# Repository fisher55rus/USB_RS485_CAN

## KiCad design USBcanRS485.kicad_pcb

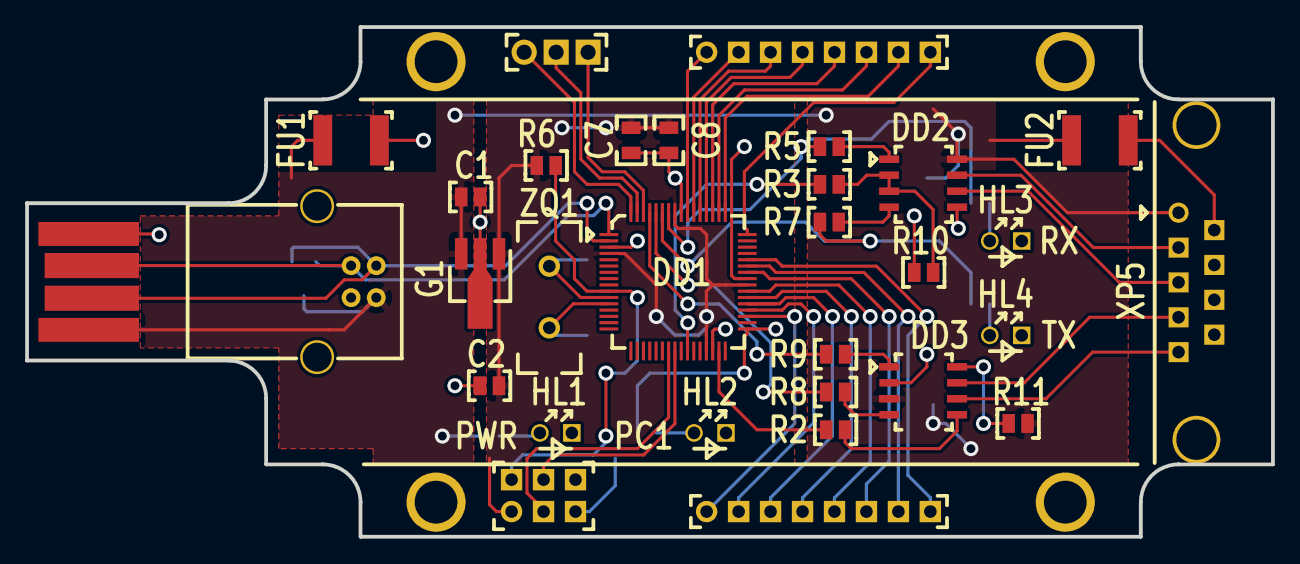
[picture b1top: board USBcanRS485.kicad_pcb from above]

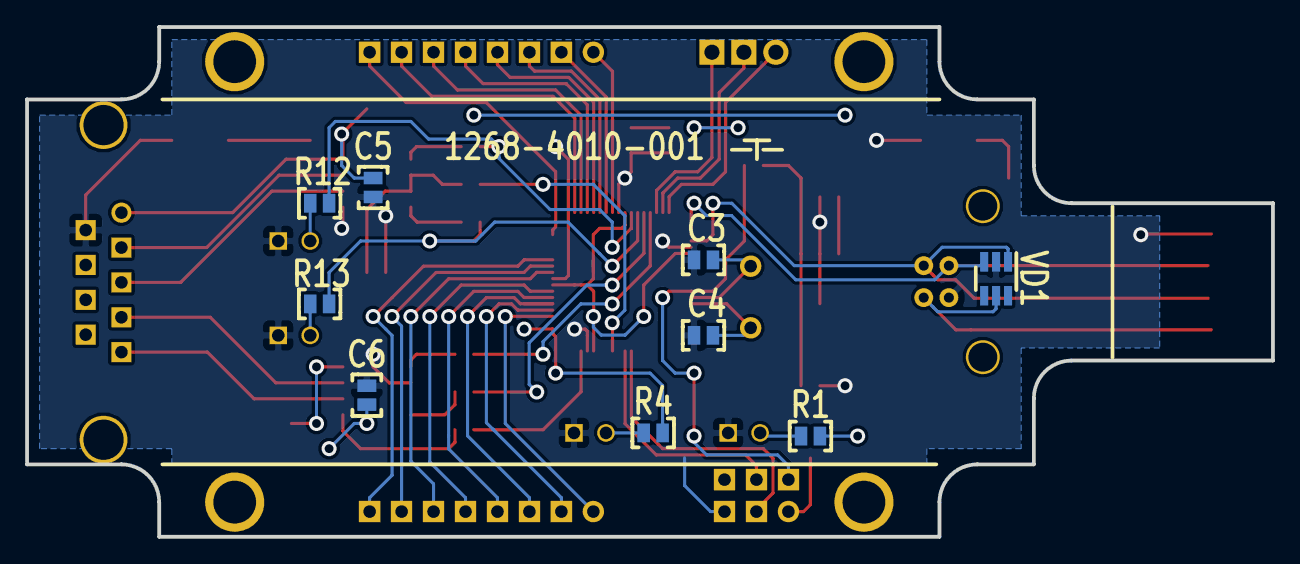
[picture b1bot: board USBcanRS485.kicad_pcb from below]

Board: 2 copper layers, 99.0 x 40.5 mm, 41 parts (10 on the bottom side), 51 nets.

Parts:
C1: 25В-0,33мкФ; Конденсатор_SMD_0603
C2: 25В-0,1мкФ; Конденсатор_SMD_0603
C3, C4: 12пФ; Конденсатор_SMD_0603
C5, C6: 25В-1,5мкФ; Конденсатор_SMD_0603
C7, C8: 16В-10мкФ; Конденсатор_SMD_0805
DD1: 1986ВЕ92; Микросхема_1986ВЕ92QL
DD2: 5559ИН10; SO-8_RS485_CAN_Milandr_OTK
DD3: 5559ИН14; SO-8_RS485_CAN_Milandr_OTK
FU1, FU2: Предохранитель; Fuse_1812
G1: L78L00 SOT-89; SOT-89-3_Handsoldering
HL1, HL2, HL3, HL4: Светодиод; LED_D3.0mm
R1: 100 Ом; Конденсатор_SMD_0603
R2, R3, R5, R7, R8, R9: 240 Ом; Конденсатор_SMD_0603
R4, R12, R13: 15 Ом; Конденсатор_SMD_0603
R6, R10: 20 кОм; Конденсатор_SMD_0603
R11: 24 Ом; Конденсатор_SMD_0603
Ref**: icon_motor_micro; Знак_МОТОР_micro
VD1: ОТК_SP0504S; SOT-23-6_Handsoldering
XP1: Вилка_СНП346-4ВП21-1-В; USB_PLUG
XP2: Вилка_СНП346-6ВП21-1-В; Вилка_PLD6_вертикальная
XP3, XP4: Вилка_СНП346-8ВП21-1-В; Вилка_PLS8_вертикальная
XP5: Вилка_СНП346-6ВП21-1-В; DSUB-9_Female
XP6: Вилка_СНП346-4ВП21-1-В; USB_B
XP7: Вилка_СНП346-3ВП21-1-В
ZQ1: РК456МДУ; Резонатор_РК456МДУ(DIP)

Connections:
3B: C2.1, C7.1, C8.1, DD1.4, DD1.29, DD1.40, DD1.57, G1.1, R6.2, XP2.1
5В: C1.1, C5.1, C6.1, DD2.8, DD3.3, FU1.1, FU2.1, G1.3, R1.2, R11.2, VD1.5, XP1.1, XP5.1, XP6.1
/Osc+: C3.2, DD1.11, ZQ1.1
/Osc-: C4.2, DD1.12, ZQ1.2
A: DD2.6, XP5.3
B: DD2.7, XP5.2
C2RX: DD3.4, R8.2
C2TX: DD3.1, R9.2
D+: DD1.1, VD1.3, XP1.3, XP6.3
D-: DD1.2, VD1.1, XP1.2, XP6.2
GND: C1.2, C2.2, C3.1, C4.1, C5.2, C6.2, C7.2, C8.2, DD1.3, DD1.30, DD1.41, DD1.56, DD2.5, DD3.2, FU1.2, FU2.2, G1.2, HL1.2, HL2.2, HL3.2, HL4.2, R10.2, VD1.2, XP1.4, XP2.5, XP5.6, XP6.4
H: DD3.7, XP5.4
L: DD3.6, XP5.5
unnamed: DD1.26, R3.2
unnamed: DD1.31, R2.2
unnamed: DD1.33, R4.2
unnamed: DD1.58, R5.1, R12.1
unnamed: DD1.59, R7.1, R13.1
unnamed: DD1.60, R8.1
unnamed: DD1.61, R9.1
unnamed: DD1.62, XP7.3
unnamed: DD1.63, XP7.2
unnamed: DD1.64, XP7.1
unnamed: DD3.8, R11.1
unnamed: HL1.1, R1.1
unnamed: HL2.1, R4.1
unnamed: HL3.1, R12.2
unnamed: HL4.1, R13.2
PA0: DD1.55, XP4.1
PA1: DD1.54, XP4.2
PA2: DD1.53, XP4.3
PA3: DD1.52, XP4.4
PA4: DD1.51, XP4.5
PA5: DD1.50, XP4.6
PA6: DD1.49, XP4.7
PA7: DD1.48, XP4.8
PB0: DD1.35, XP3.1
PB1: DD1.36, XP3.2
PB2: DD1.37, XP3.3
PB3: DD1.38, XP3.4
PB4: DD1.39, XP3.5
PB5: DD1.42, XP3.6
PB6: DD1.43, XP3.7
PB7: DD1.44, XP3.8
PE1-RSen: DD2.2, DD2.3, R3.1, R10.1
PE2-CANen: DD3.5, R2.1
RESET: DD1.10, R6.1, XP2.2
TCK: DD1.24, XP2.4
TMS: DD1.23, XP2.3
U2RX: DD2.1, R5.2
U2TX: DD2.4, R7.2

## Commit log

2019-01-08 Первая зарузка
    Пробую загрузить файлы
2019-01-08 Кажется разобрался
    Или не кажется
2019-01-08 Выполнена трассировка
    Осталось соединить полигоны
2019-01-14 Проект почти закончен
    Осталось добавить предохранители на вход и выход
2019-01-16 Доработка проекта
    Плата приведена к размерам корпуса G403. Добавлены предохранители.
    Привязаны актуальные 3D-модели.
2019-01-16 Добавлена 3D - модель платы
